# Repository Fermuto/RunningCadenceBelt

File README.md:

# RunningCadenceBelt

Running cadence is the number of steps a runner takes per minute while running, commonly measured in strides per minute (SPM). It is a useful measurement for runners as it can provide insight into efficiency, form, and stride length. An ideal cadence for most runners typically falls into the range of 170 to 180 SPM although this is dependent on height and pace.

Currently, there are already products on the market that can measure running cadence. For example, most “running watches” have cadence as an included measurement. However, it can be cumbersome for runners to constantly switch through display screens to monitor multiple data points at the same time such as pace, heart rate, distance, and cadence. Furthermore, unless a runner is running with their arm locked in front of them, continuous monitoring of cadence is impossible with a running watch. Other products take a different approach such as the foot-mounted ARION Footpod non-GPS 1.0 and Stryd. These products can track the cadence throughout the run in much the same way that a running watch would, but they can’t provide that information to the runner without the use of a watch or smartphone. In both the watch and foot-mounted solution, there is a lack of a product that provides easy, hands-free haptic feedback to the runner informing them when their cadence falls outside of the ideal cadence range.

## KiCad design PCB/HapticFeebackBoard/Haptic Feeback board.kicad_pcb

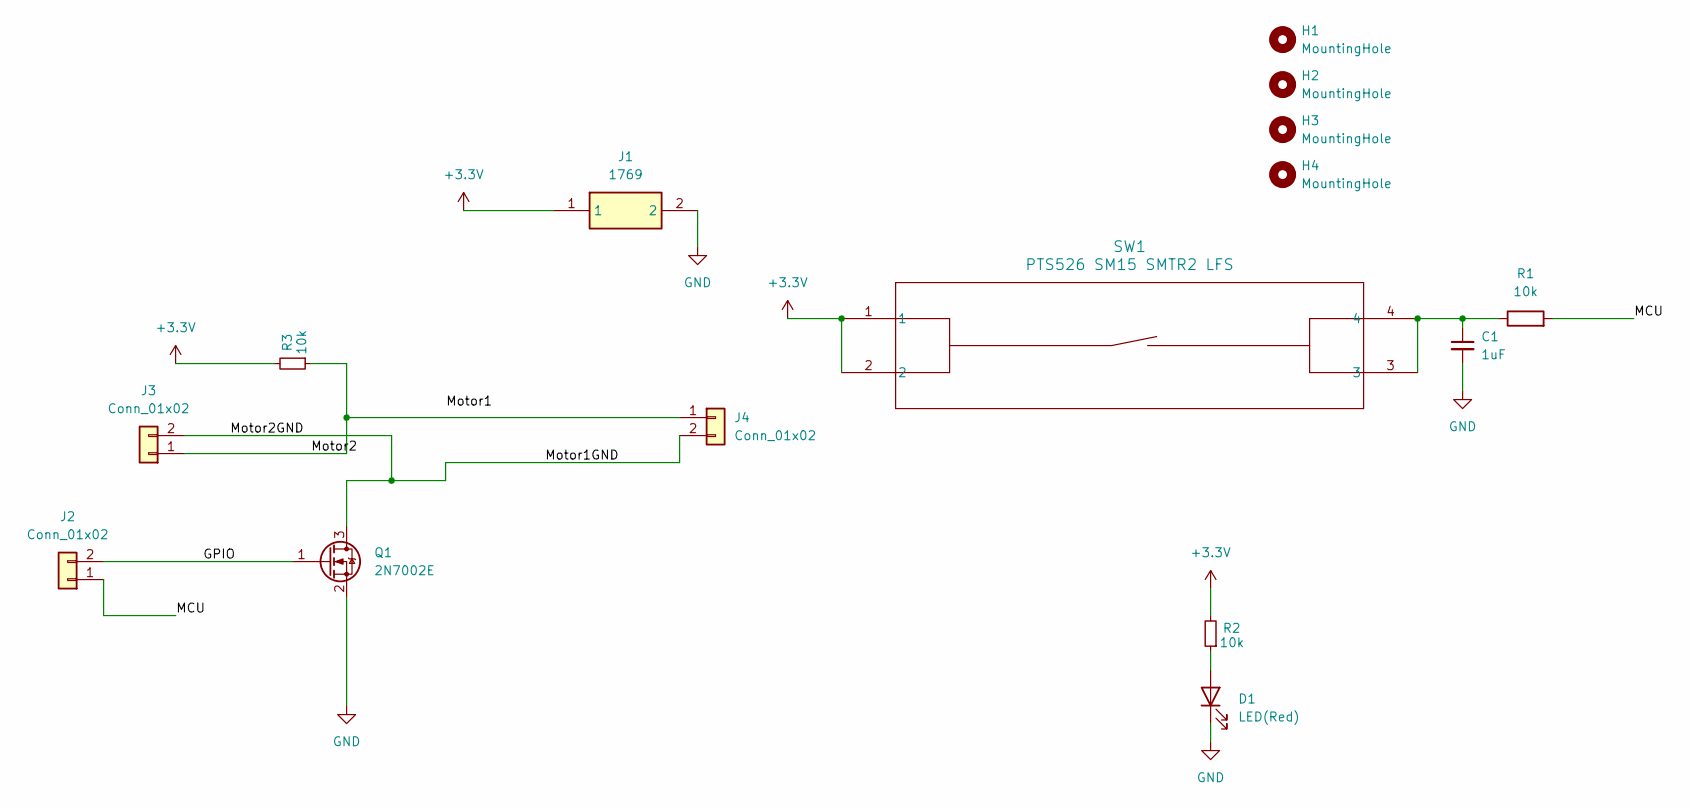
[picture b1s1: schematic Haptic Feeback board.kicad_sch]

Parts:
C1: 1uF; C_0805_2012Metric_Pad1.18x1.45mm_HandSolder
D1: LED(Red); LED_0603_1608Metric_Pad1.05x0.95mm_HandSolder
H1, H2, H3, H4: MountingHole; MountingHole_3.2mm_M3
J1: 1769; Mouser Part Number 485-1769
J2, J3, J4: Conn_01x02; Molex_KK-254_AE-6410-02A_1x02_P2.54mm_Vertical
Q1: 2N7002E; SOT-23-3
R1, R2, R3: 10k; R_0805_2012Metric_Pad1.20x1.40mm_HandSolder
SW1: PTS526 SM15 SMTR2 LFS; SON4_PTS526 SM15 SMTR2 LFS_CNK

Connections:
+3.3V: J1.1, R2.2, R3.2, SW1.1, SW1.2
/GPIO: J2.2, Q1.1 (G)
/MCU: J2.1, R1.2
/Motor1GND: J3.2, J4.2, Q1.3 (D)
/Motor2: J3.1, J4.1, R3.1
GND: C1.2, D1.1 (K), J1.2, Q1.2 (S)
unnamed: C1.1, R1.1, SW1.3, SW1.4
unnamed: D1.2 (A), R2.1

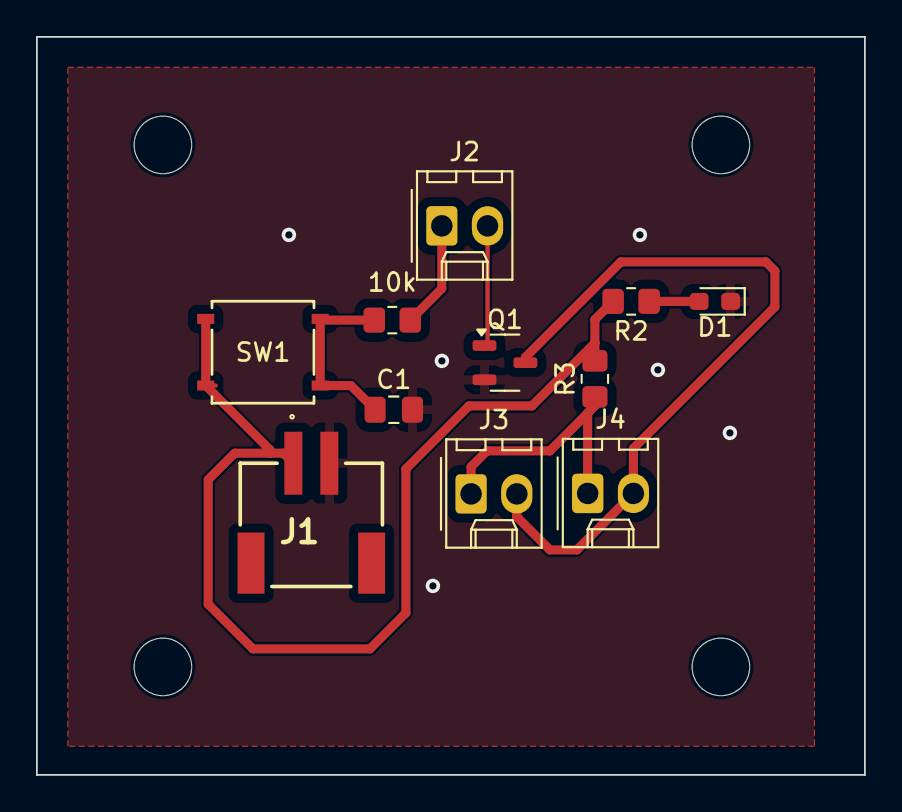
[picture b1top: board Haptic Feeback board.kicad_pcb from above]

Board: 2 copper layers, 46.0 x 41.0 mm, 15 parts (0 on the bottom side), 8 nets.

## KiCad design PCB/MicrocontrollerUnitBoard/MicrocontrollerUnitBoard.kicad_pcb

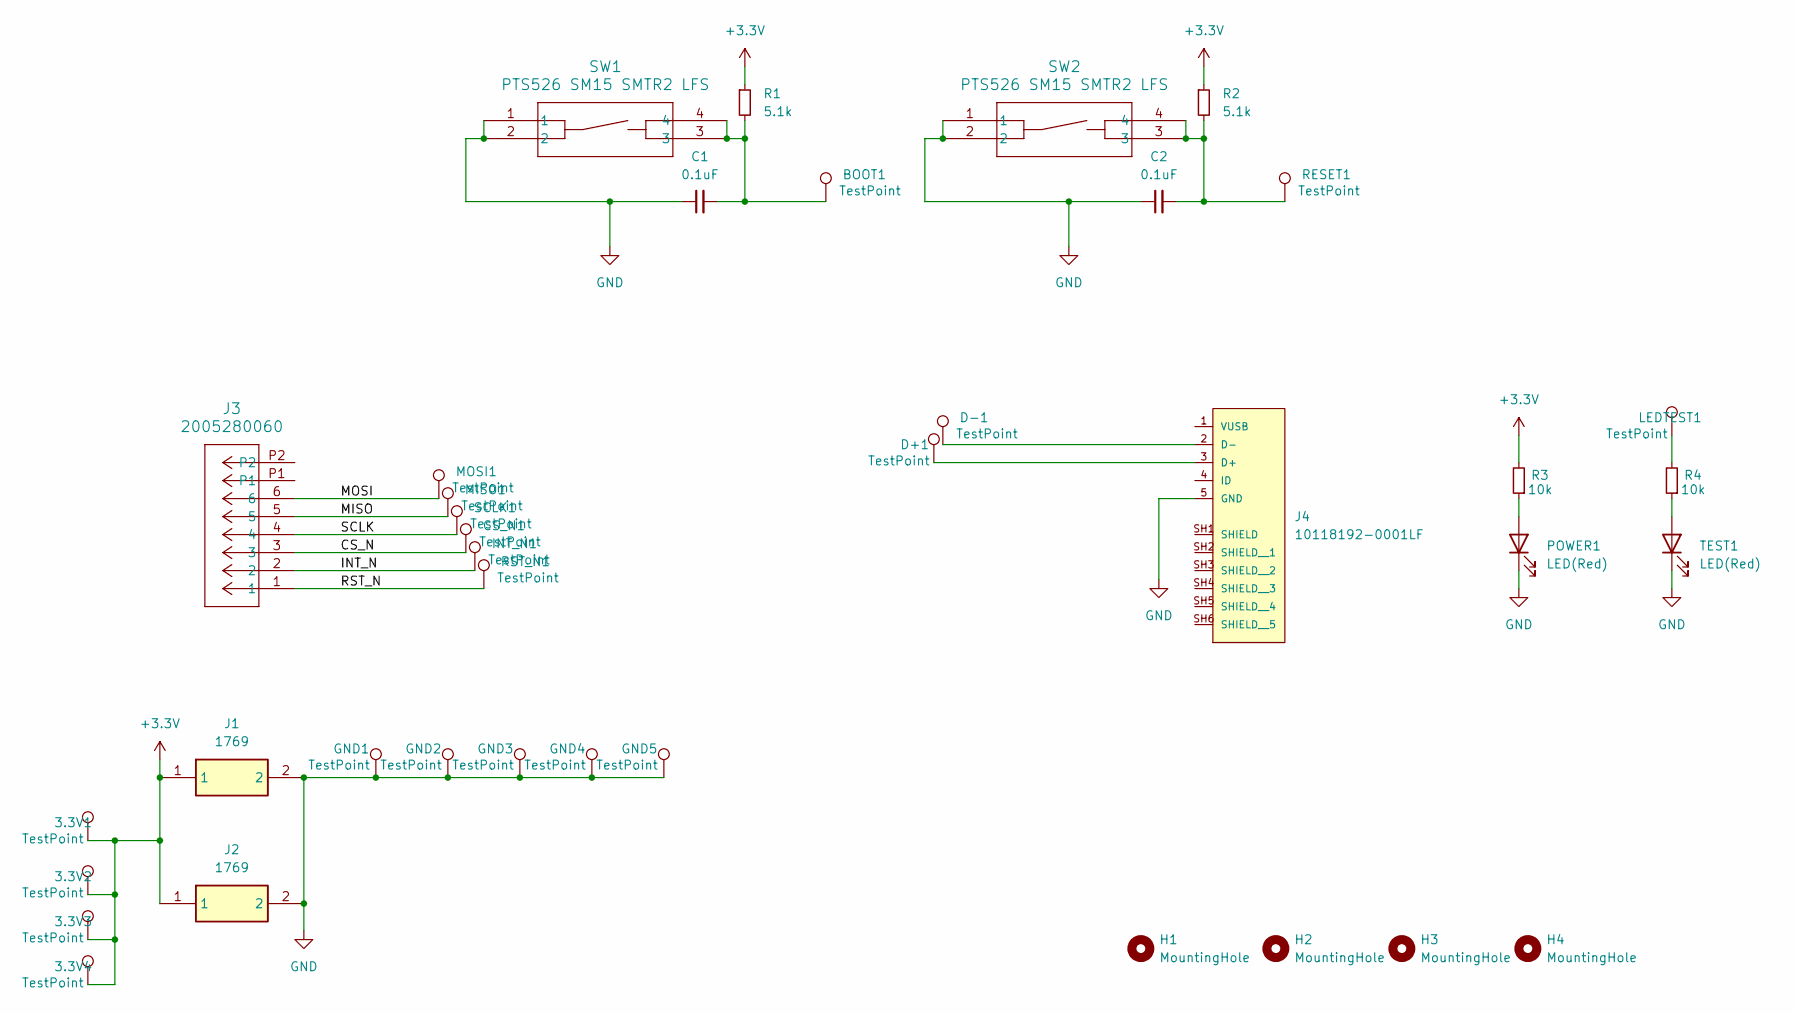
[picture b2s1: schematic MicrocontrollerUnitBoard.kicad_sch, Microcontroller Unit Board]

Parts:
3.3V1, 3.3V2, 3.3V3, 3.3V4: TestPoint; TestPoint_THTPad_D2.0mm_Drill1.0mm
BOOT1: TestPoint; TestPoint_THTPad_D2.0mm_Drill1.0mm
C1, C2: 0.1uF; C_0805_2012Metric_Pad1.18x1.45mm_HandSolder
CS_N1: TestPoint; TestPoint_THTPad_D2.0mm_Drill1.0mm
D+1: TestPoint; TestPoint_THTPad_D2.0mm_Drill1.0mm
D-1: TestPoint; TestPoint_THTPad_D2.0mm_Drill1.0mm
GND1, GND2, GND3, GND4, GND5: TestPoint; TestPoint_THTPad_D2.0mm_Drill1.0mm
H1, H2, H3, H4: MountingHole; MountingHole_3.2mm_M3
INT_N1: TestPoint; TestPoint_THTPad_D2.0mm_Drill1.0mm
J1, J2: 1769; Mouser Part Number 485-1769
J3: 2005280060; CON_2005280060_MOL
J4: 10118192-0001LF; AMPHENOL_10118192-0001LF; PARTREV B
LEDTEST1: TestPoint; TestPoint_THTPad_D2.0mm_Drill1.0mm
MISO1: TestPoint; TestPoint_THTPad_D2.0mm_Drill1.0mm
MOSI1: TestPoint; TestPoint_THTPad_D2.0mm_Drill1.0mm
POWER1: LED(Red); LED_0603_1608Metric_Pad1.05x0.95mm_HandSolder
R1, R2: 5.1k; R_0805_2012Metric_Pad1.20x1.40mm_HandSolder
R3, R4: 10k; R_0805_2012Metric_Pad1.20x1.40mm_HandSolder
RESET1: TestPoint; TestPoint_THTPad_D2.0mm_Drill1.0mm
RST_N1: TestPoint; TestPoint_THTPad_D2.0mm_Drill1.0mm
SCLK1: TestPoint; TestPoint_THTPad_D2.0mm_Drill1.0mm
SW1, SW2: PTS526 SM15 SMTR2 LFS; SON4_PTS526 SM15 SMTR2 LFS_CNK
TEST1: LED(Red); LED_0603_1608Metric_Pad1.05x0.95mm_HandSolder

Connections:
+3.3V: 3.3V1.1, 3.3V2.1, 3.3V3.1, 3.3V4.1, J1.1, J2.1, R1.1, R2.1, R3.2
/CS_N: CS_N1.1, J3.3
/INT_N: INT_N1.1, J3.2
/MISO: J3.5, MISO1.1
/MOSI: J3.6, MOSI1.1
/RST_N: J3.1, RST_N1.1
/SCLK: J3.4, SCLK1.1
GND: C1.1, C2.1, GND1.1, GND2.1, GND3.1, GND4.1, GND5.1, J1.2, J2.2, J4.5 (GND), POWER1.1 (K), SW1.1, SW1.2, SW2.1, SW2.2, TEST1.1 (K)
unnamed: BOOT1.1, C1.2, R1.2, SW1.3, SW1.4
unnamed: C2.2, R2.2, RESET1.1, SW2.3, SW2.4
unnamed: D+1.1, J4.3 (D+)
unnamed: D-1.1, J4.2 (D-)
unnamed: LEDTEST1.1, R4.2
unnamed: POWER1.2 (A), R3.1
unnamed: R4.1, TEST1.2 (A)

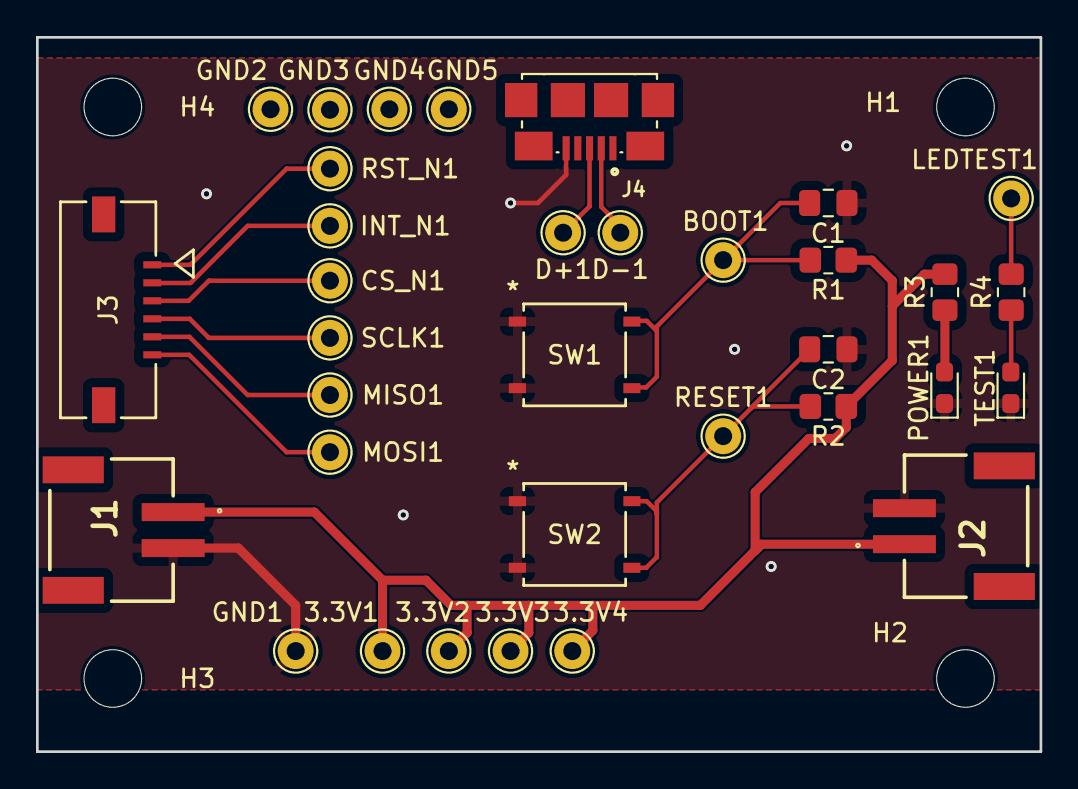
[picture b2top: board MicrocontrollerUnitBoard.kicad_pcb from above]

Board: 2 copper layers, 55.8 x 39.7 mm, 38 parts (0 on the bottom side), 15 nets.

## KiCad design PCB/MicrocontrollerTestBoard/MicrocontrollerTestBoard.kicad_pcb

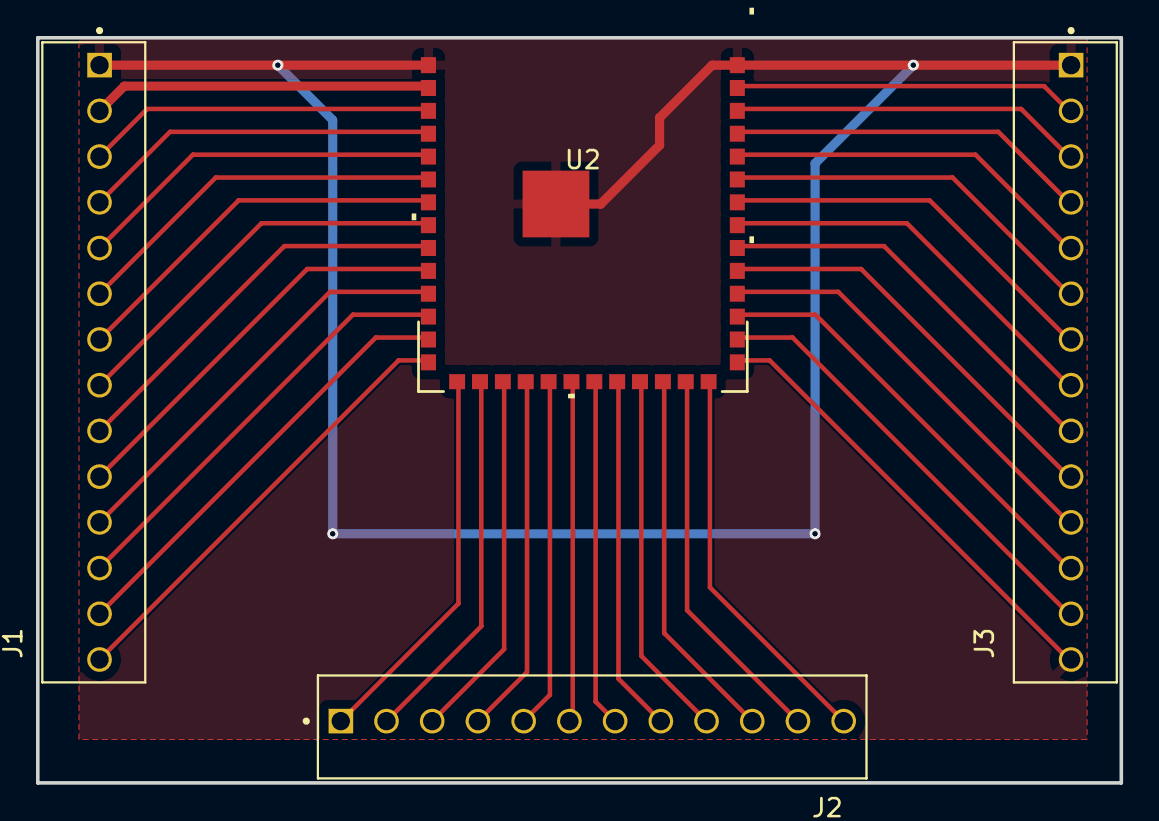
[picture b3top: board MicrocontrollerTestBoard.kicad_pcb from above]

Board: 2 copper layers, 60.2 x 41.4 mm, 4 parts (0 on the bottom side), 38 nets.

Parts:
J1, J3: 1-640456-4; Connector Header Through Hole 14 position 0.100 (2.54mm)
J2: 1-640456-2; Connector Header Through Hole 12 position 0.100 (2.54mm)
U2: ESP32-S3-WROOM-1-N16; ESP32-S3-WROOM-1_EXP

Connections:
unnamed: J1.2, U2.2 (3V3)
unnamed: J1.3, U2.3 (EN)
unnamed: J1.1, J3.1, J3.14, U2.1 (GND), U2.40 (GND), U2.41 (EPAD)
unnamed: J3.13, U2.27 (IO0)
unnamed: J3.2, U2.38 (IO2)
unnamed: J2.1, U2.15 (IO3)
unnamed: J1.4, U2.4 (IO4)
unnamed: J1.5, U2.5 (IO5)
unnamed: J1.6, U2.6 (IO6)
unnamed: J1.7, U2.7 (IO7)
unnamed: J1.12, U2.12 (IO8)
unnamed: J2.3, U2.17 (IO9)
unnamed: J2.4, U2.18 (IO10)
unnamed: J2.5, U2.19 (IO11)
unnamed: J2.6, U2.20 (IO12)
unnamed: J2.7, U2.21 (IO13)
unnamed: J2.8, U2.22 (IO14)
unnamed: J1.8, U2.8 (IO15)
unnamed: J1.9, U2.9 (IO16)
unnamed: J1.10, U2.10 (IO17)
unnamed: J1.11, U2.11 (IO18)
unnamed: J1.13, U2.13 (IO19)
unnamed: J1.14, U2.14 (IO20)
unnamed: J2.9, U2.23 (IO21)
unnamed: J3.12, U2.28 (IO35_B)
unnamed: J3.11, U2.29 (IO36_B)
unnamed: J3.10, U2.30 (IO37_B)
unnamed: J3.9, U2.31 (IO38)
unnamed: J3.8, U2.32 (IO39)
unnamed: J3.7, U2.33 (IO40)
unnamed: J3.6, U2.34 (IO41)
unnamed: J3.5, U2.35 (IO42)
unnamed: J2.12, U2.26 (IO45)
unnamed: J2.2, U2.16 (IO46)
unnamed: J2.10, U2.24 (IO47)
unnamed: J2.11, U2.25 (IO48)
unnamed: J3.4, U2.36 (RXD0)
unnamed: J3.3, U2.37 (TXD0)

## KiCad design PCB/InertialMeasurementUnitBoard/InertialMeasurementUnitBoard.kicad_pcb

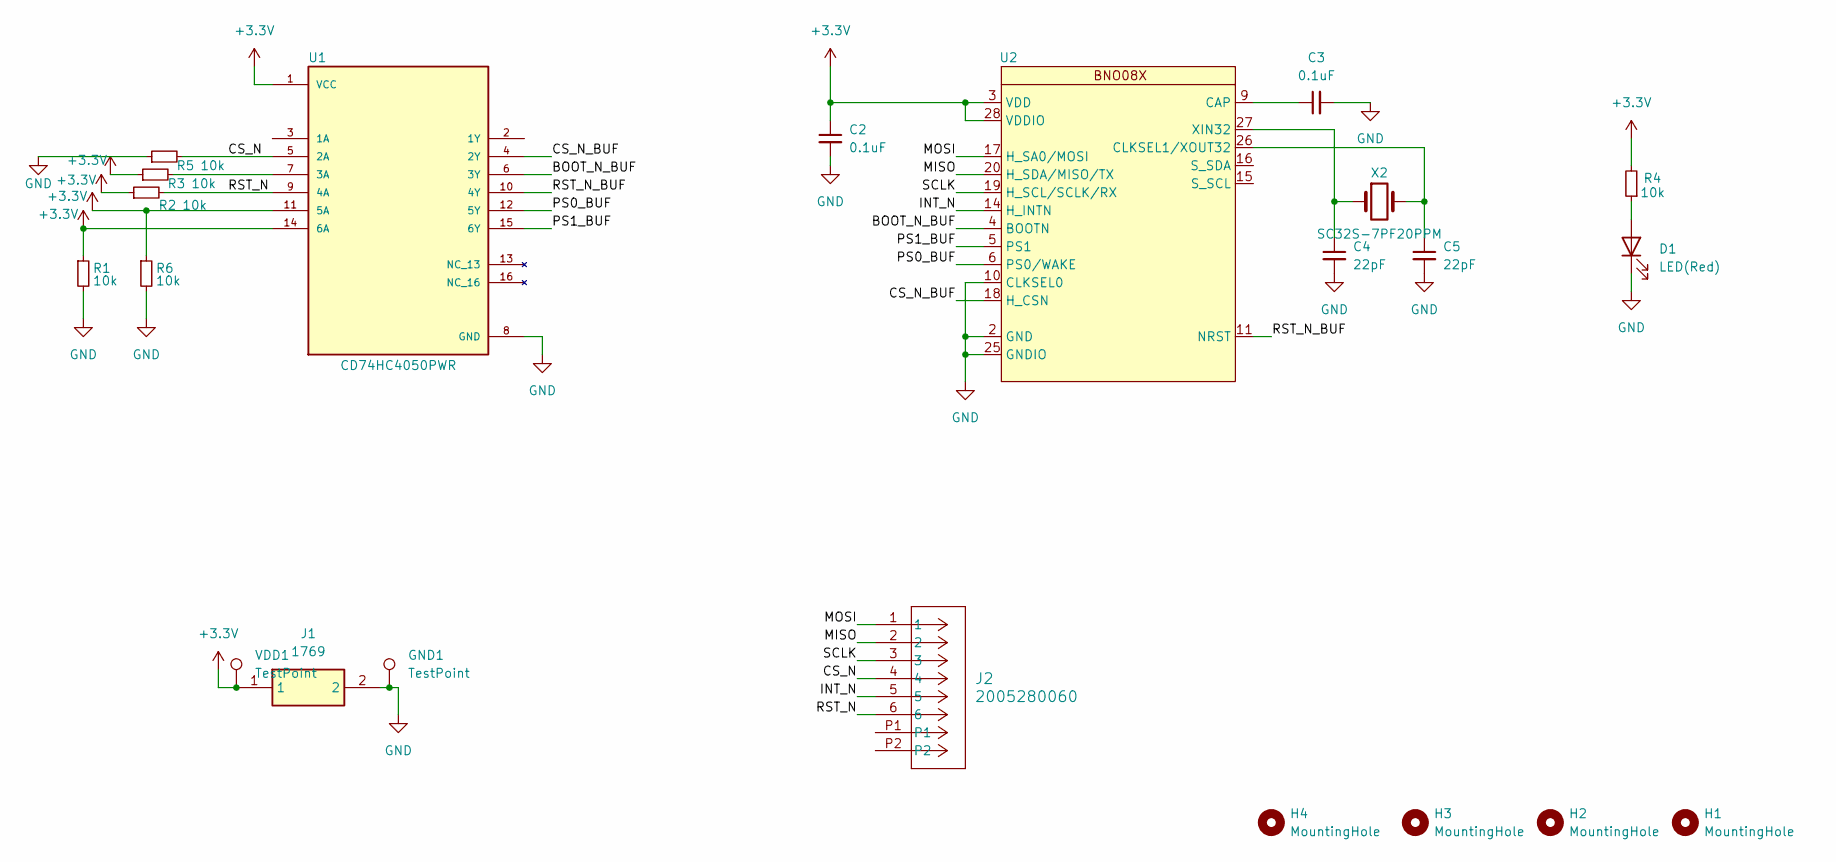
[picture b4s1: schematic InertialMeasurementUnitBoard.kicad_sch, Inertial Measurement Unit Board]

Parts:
C2, C3: 0.1uF; C_0805_2012Metric_Pad1.18x1.45mm_HandSolder
C4, C5: 22pF; C_0603_1608Metric_Pad1.08x0.95mm_HandSolder
D1: LED(Red); LED_0603_1608Metric_Pad1.05x0.95mm_HandSolder
GND1: TestPoint; TestPoint_THTPad_D2.0mm_Drill1.0mm
H1, H2, H3, H4: MountingHole; MountingHole_3.2mm_M3
J1: 1769; Mouser Part Number 485-1769
J2: 2005280060; CON_2005280060_MOL
R1, R2, R3, R4, R5, R6: 10k; R_0805_2012Metric_Pad1.20x1.40mm_HandSolder
U1: CD74HC4050PWR; SOP65P640X120-16N; PARTREV February 2005
U2: IC_BNO080
VDD1: TestPoint; TestPoint_THTPad_D2.0mm_Drill1.0mm
X2: SC32S-7PF20PPM; XTAL_SC32S-7PF20PPM_EPS

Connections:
+3.3V: C2.1, J1.1, R1.1, R2.1, R3.1, R4.2, R6.1, U1.1 (VCC), U1.11 (5A), U1.14 (6A), U2.3 (VDD), U2.28 (VDDIO), VDD1.1
/BOOT_N_BUF: U1.6 (3Y), U2.4 (BOOTN)
/CS_N: J2.4, R5.2, U1.5 (2A)
/CS_N_BUF: U1.4 (2Y), U2.18 (H_CSN)
/INT_N: J2.5, U2.14 (H_INTN)
/MISO: J2.2, U2.20 (H_SDA/MISO/TX)
/MOSI: J2.1, U2.17 (H_SA0/MOSI)
/PS0_BUF: U1.12 (5Y), U2.6 (PS0/WAKE)
/PS1_BUF: U1.15 (6Y), U2.5 (PS1)
/RST_N: J2.6, R2.2, U1.9 (4A)
/RST_N_BUF: U1.10 (4Y), U2.11 (NRST)
/SCLK: J2.3, U2.19 (H_SCL/SCLK/RX)
GND: C2.2, C3.2, C4.2, C5.2, D1.1 (K), GND1.1, J1.2, R1.2, R5.1, R6.2, U1.8 (GND), U2.2 (GND), U2.10 (CLKSEL0), U2.25 (GNDIO)
unnamed: D1.2 (A), R4.1
unnamed: R3.2, U1.7 (3A)
unnamed: C3.1, U2.9 (CAP)
unnamed: C5.1, U2.26 (CLKSEL1/XOUT32), X2.2
unnamed: C4.1, U2.27 (XIN32), X2.1

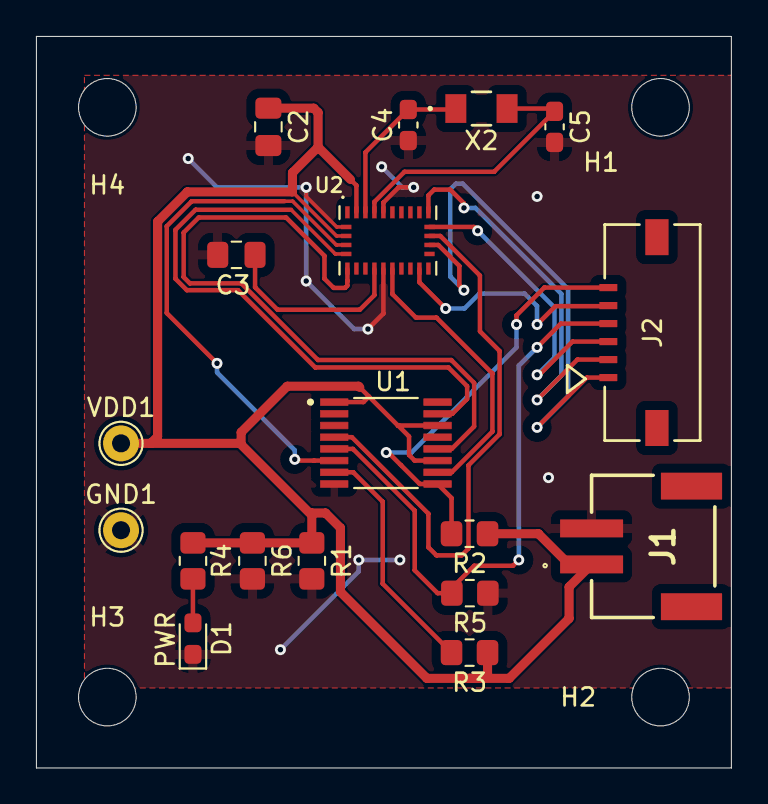
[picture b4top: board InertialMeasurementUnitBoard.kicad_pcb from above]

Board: 2 copper layers, 38.6 x 40.6 mm, 22 parts (0 on the bottom side), 18 nets.

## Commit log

2024-02-29 Add BNO086 footprint/symbol, add ESP32-S3 symbol
    ESP32 symbol redundant
2024-02-29 Create IMU Board, MCU Board projects
2024-02-29 Reorganize into PCB folder
2024-02-29 Add CD74HC4050PWR symbol, footprint
2024-02-29 Move BNO08X footprint
2024-02-29 Initial work on IMU board
    Some configuration work done; added power LED
2024-02-29 Add PTS526 SM15 SMTR2 LFS footprint/symbol
2024-02-29 Finish IMU schematic
2024-02-29 Add SC32S-7PF20PPM footprint/symbol
2024-02-29 Add 2-pin JST, 6-7-9-pin FFC conn footprint/symbol
2024-02-29 2/29 IMU Board
    Added connectors to schematic, started layout
2024-02-29 Started Haptic Feedback Board Schematic
2024-03-01 Updated Haptic Feedback Board
    Should be close to final schematic
2024-03-01 Initial completion of Inertial Measurement Unit Board
    Add test points for BMS outputs, complete layout.
2024-03-01 Support on haptic feedback board
    Added schematic details, imported PCBWay DRC
2024-03-01 Small edits to IMU board layout
    Tidying up of silkscreen, traces, fab, etc.
2024-03-01 Update IMU board schematic details
2024-03-01 3/1 MCU Board progress upload for board review
2024-03-03 Create microcontroller test board
2024-03-03 Finished Haptic Feedback Board
2024-03-03 Revert "Attempting to push"
    This reverts commit dba7137e2b6d79e6a799e918ac76b279f377e3a9, reversing
    changes made to e00eed14296bda41403d05f06b408ec44583351d.
2024-03-03 Revert "Finished Haptic Feedback Board"
    This reverts commit e00eed14296bda41403d05f06b408ec44583351d.
2024-03-03 Pushing Haptic Feedback
2024-03-03 recovery attempt
2024-03-03 Recovery attempt 2
2024-03-03 Update IMU Board thicker power trace
2024-03-03 Create MicrocontrollerTestBoard
2024-03-03 Updating Haptic Feedback Board
2024-03-03 Update trace widths IMU
2024-03-03 Edits to Haptic Feedback
2024-03-04 Generated Gerber Files
2024-03-04 Minor copper pour adjustments
2024-03-04 Further minor edits, added power LED
2024-03-04 Small updates on IMU, initial finish of MCU
2024-03-04 Add male header, ESP32-S3-WROOM-1 symbols/footprints
2024-03-04 Finish MCU Test board
2024-03-04 Create MCU Test gerbers, drill, passes audit
2024-03-04 Final pass for 1st round order, generate gerbers for all, all pass audit
2024-03-16 Adding IMU Example Code + Environment Setup Insturctions
2024-03-22 Added Crude Step-Count Algorithm, and a Python Code which builds Low-Pass Filters
2024-03-27 Upload of zips used in 1st round pcb order
2024-04-02 Updated Haptic Feedback Board
    Changed motor to be connected to the drain rather than source
2024-04-02 updating ESP32 and BNO08x code
2024-04-03 Making minor improvements/fixes to code
2024-04-04 Making minor improvements/changes
2024-04-10 Updating Code
2024-04-12 Made changes to code during troubleshooting
2024-04-16 Added 3D print file
    Added 3D print file. The print may be too heavy and not have enough space.
2024-04-20 Laptop algorithm upload
2024-04-20 Desktop algorithm upload
    Algorithm verification, testing and tweaking before porting
2024-04-22 arduino upload
2024-04-23 Initial demo "ready" version
2024-04-23 update; ino improvements, python graph generation
2024-04-24 final revision for final demo
